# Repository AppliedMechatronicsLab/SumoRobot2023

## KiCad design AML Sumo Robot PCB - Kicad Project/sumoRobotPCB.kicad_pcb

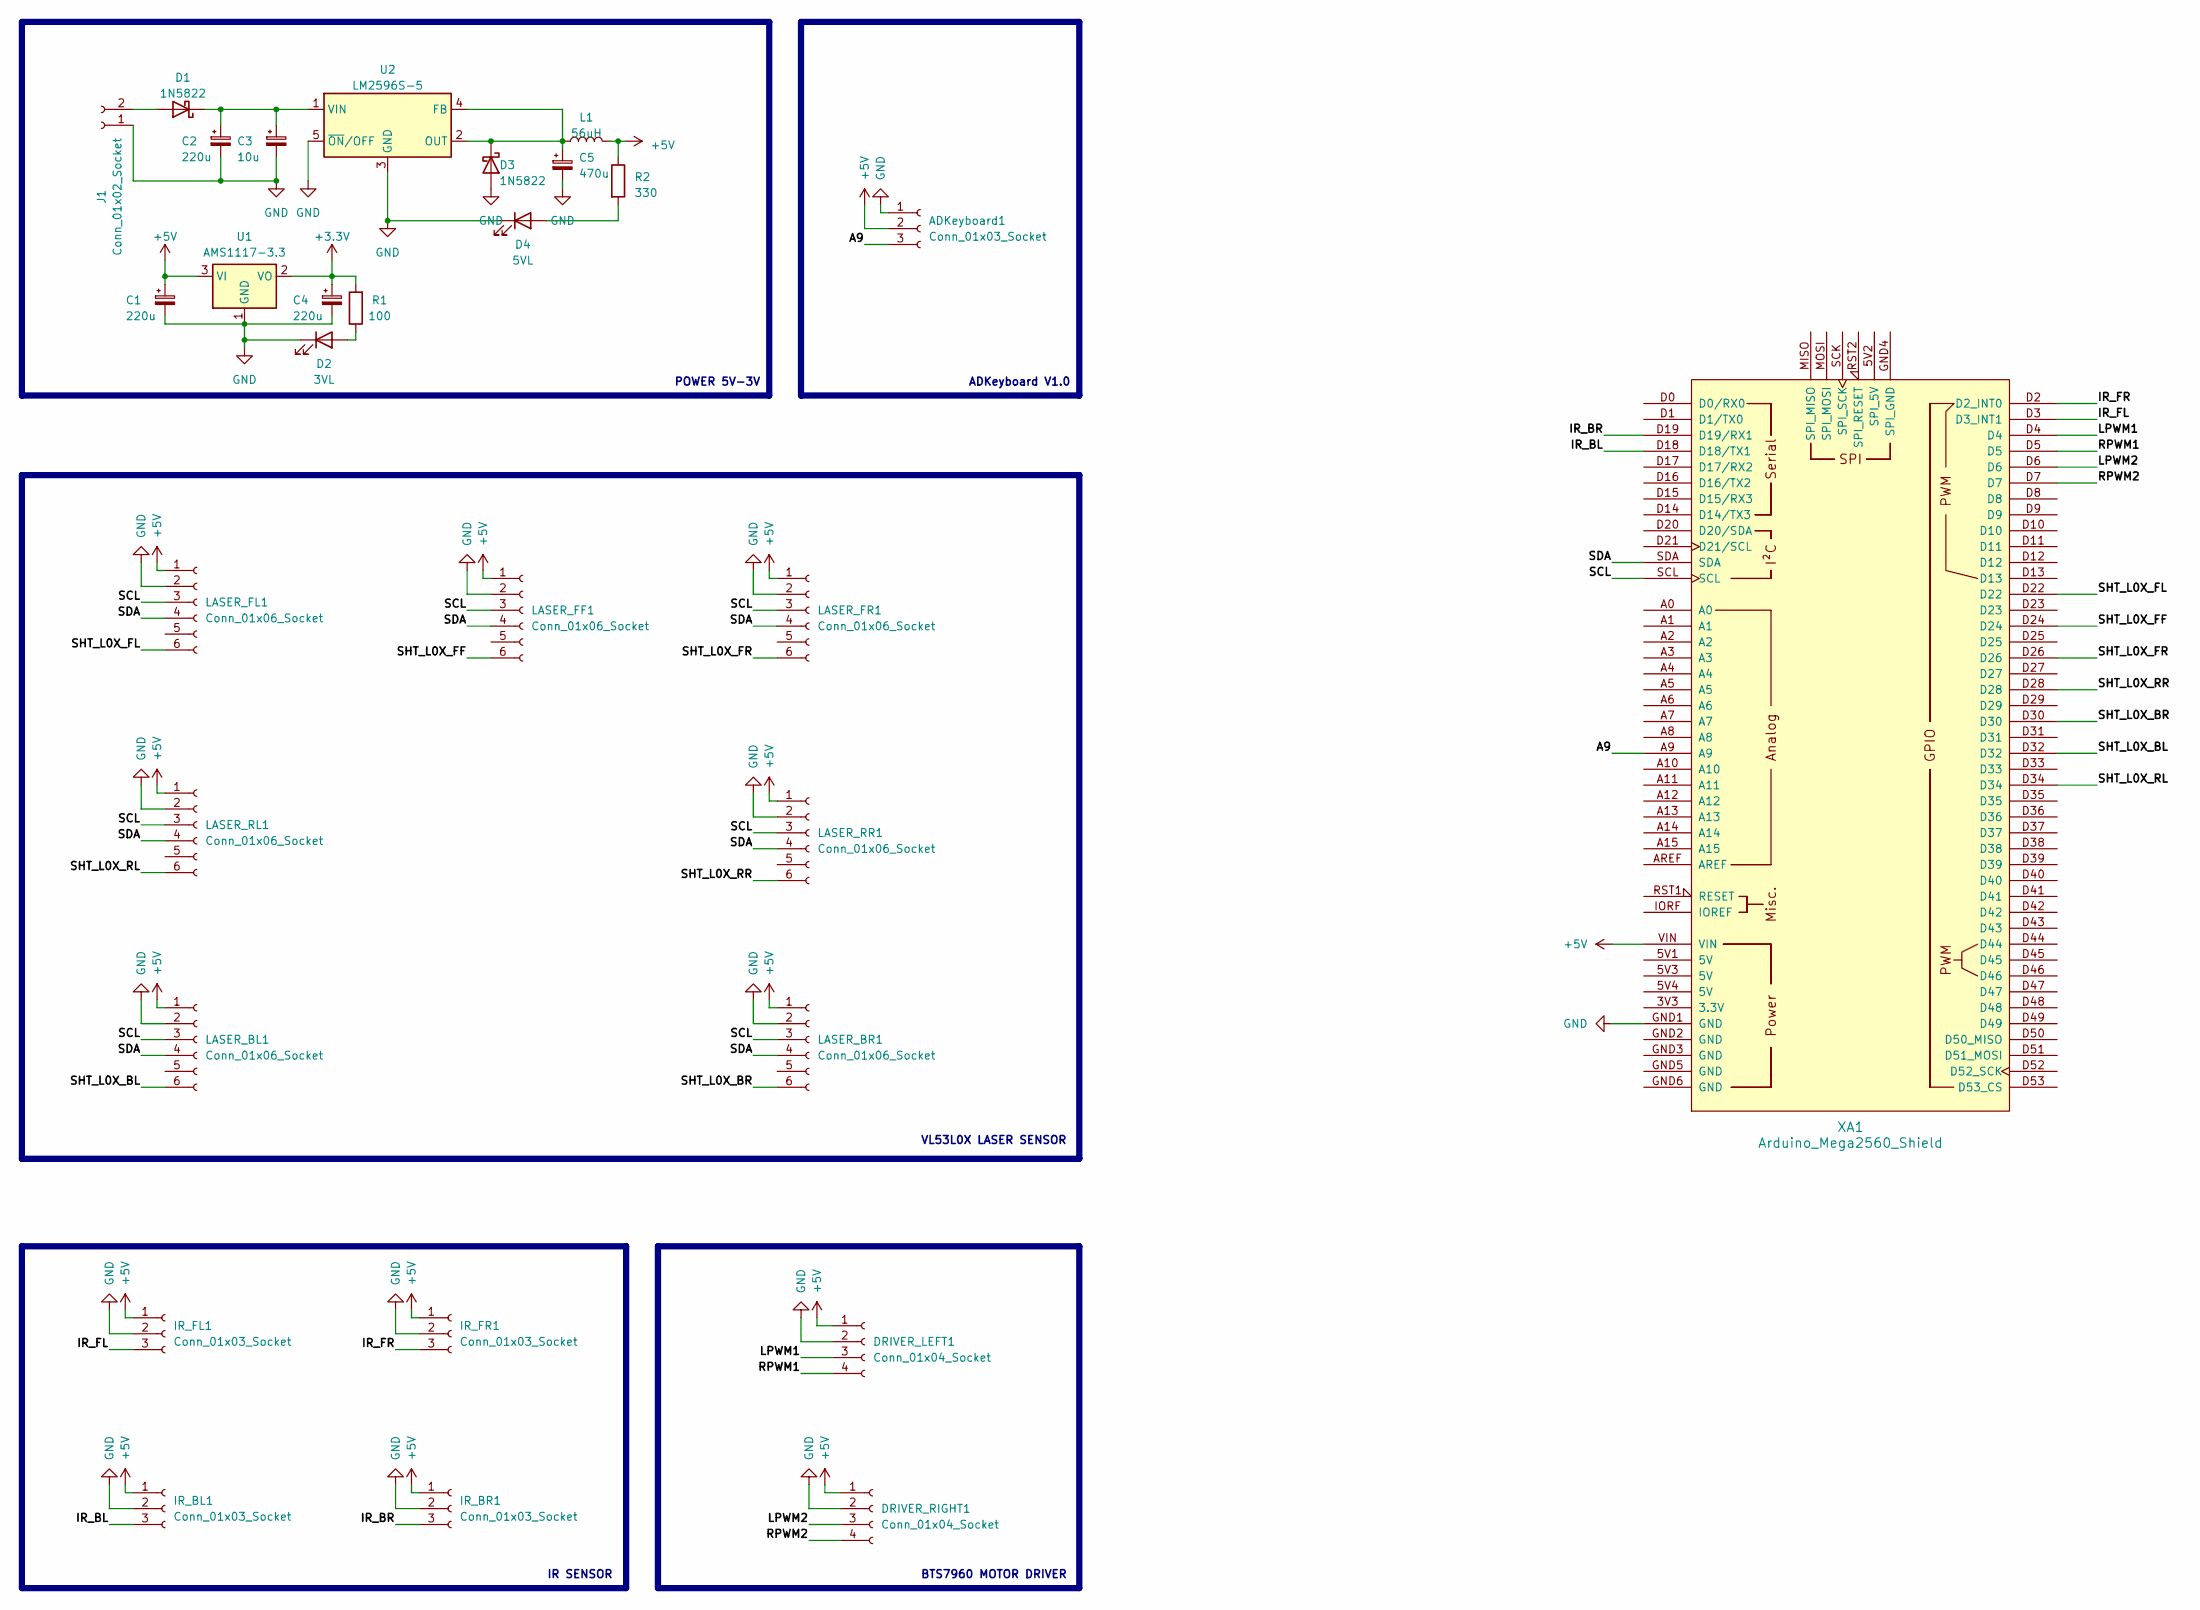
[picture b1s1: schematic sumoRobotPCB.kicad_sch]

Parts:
ADKeyboard1: Conn_01x03_Socket; PinHeader_1x03_P2.54mm_Vertical
C1, C2, C4: 220u; CP_Elec_8x10
C3: 10u; R_0805_2012Metric
C5: 470u; CP_Elec_8x10
D1, D3: 1N5822; D_SMA
D2: 3VL; LED_1206_3216Metric
D4: 5VL; LED_1206_3216Metric
DRIVER_LEFT1: Conn_01x04_Socket; PinHeader_1x04_P2.54mm_Vertical
DRIVER_RIGHT1: Conn_01x04_Socket; PinHeader_1x04_P2.54mm_Vertical
IR_BL1: Conn_01x03_Socket; PinHeader_1x03_P2.54mm_Vertical
IR_BR1: Conn_01x03_Socket; PinHeader_1x03_P2.54mm_Vertical
IR_FL1: Conn_01x03_Socket; PinHeader_1x03_P2.54mm_Vertical
IR_FR1: Conn_01x03_Socket; PinHeader_1x03_P2.54mm_Vertical
J1: Conn_01x02_Socket; JST_VH_B2P-VH_1x02_P3.96mm_Vertical
L1: 56uH
LASER_BL1: Conn_01x06_Socket; PinHeader_1x06_P2.54mm_Vertical
LASER_BR1: Conn_01x06_Socket; PinHeader_1x06_P2.54mm_Vertical
LASER_FF1: Conn_01x06_Socket; PinHeader_1x06_P2.54mm_Vertical
LASER_FL1: Conn_01x06_Socket; PinHeader_1x06_P2.54mm_Vertical
LASER_FR1: Conn_01x06_Socket; PinHeader_1x06_P2.54mm_Vertical
LASER_RL1: Conn_01x06_Socket; PinHeader_1x06_P2.54mm_Vertical
LASER_RR1: Conn_01x06_Socket; PinHeader_1x06_P2.54mm_Vertical
R1: 100; R_0805_2012Metric
R2: 330; R_0805_2012Metric
U1: AMS1117-3.3; SOT-223-3_TabPin2
U2: LM2596S-5; TO-263-5_TabPin3
XA1: Arduino_Mega2560_Shield

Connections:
+3.3V: C4.1, R1.2, U1.2 (VO)
+5V: ADKeyboard1.2, C1.1, DRIVER_LEFT1.1, DRIVER_RIGHT1.1, IR_BL1.1, IR_BR1.1, IR_FL1.1, IR_FR1.1, L1.2, LASER_BL1.1, LASER_BR1.1, LASER_FF1.1, LASER_FL1.1, LASER_FR1.1, LASER_RL1.1, LASER_RR1.1, R2.1, U1.3 (VI), XA1.VIN
/A9: ADKeyboard1.3, XA1.A9
/IR_BL: IR_BL1.3, XA1.D18 (D18/TX1)
/IR_BR: IR_BR1.3, XA1.D19 (D19/RX1)
/IR_FL: IR_FL1.3, XA1.D3 (D3_INT1)
/IR_FR: IR_FR1.3, XA1.D2 (D2_INT0)
/LPWM1: DRIVER_LEFT1.3, XA1.D4
/LPWM2: DRIVER_RIGHT1.3, XA1.D6
/RPWM1: DRIVER_LEFT1.4, XA1.D5
/RPWM2: DRIVER_RIGHT1.4, XA1.D7
/SCL: LASER_BL1.3, LASER_BR1.3, LASER_FF1.3, LASER_FL1.3, LASER_FR1.3, LASER_RL1.3, LASER_RR1.3, XA1.SCL
/SDA: LASER_BL1.4, LASER_BR1.4, LASER_FF1.4, LASER_FL1.4, LASER_FR1.4, LASER_RL1.4, LASER_RR1.4, XA1.SDA
/SHT_L0X_BL: LASER_BL1.6, XA1.D32
/SHT_L0X_BR: LASER_BR1.6, XA1.D30
/SHT_L0X_FF: LASER_FF1.6, XA1.D24
/SHT_L0X_FL: LASER_FL1.6, XA1.D22
/SHT_L0X_FR: LASER_FR1.6, XA1.D26
/SHT_L0X_RL: LASER_RL1.6, XA1.D34
/SHT_L0X_RR: LASER_RR1.6, XA1.D28
GND: ADKeyboard1.1, C1.2, C2.2, C3.2, C4.2, C5.2, D2.1 (K), D3.2 (A), D4.1 (K), DRIVER_LEFT1.2, DRIVER_RIGHT1.2, IR_BL1.2, IR_BR1.2, IR_FL1.2, IR_FR1.2, J1.1, LASER_BL1.2, LASER_BR1.2, LASER_FF1.2, LASER_FL1.2, LASER_FR1.2, LASER_RL1.2, LASER_RR1.2, U1.1 (GND), U2.3 (GND), U2.5 (~ON/OFF), XA1.GND1 (GND)
unnamed: D1.2 (A), J1.2
unnamed: C2.1, C3.1, D1.1 (K), U2.1 (VIN)
unnamed: D2.2 (A), R1.1
unnamed: C5.1, D3.1 (K), L1.1, U2.2 (OUT), U2.4 (FB)
unnamed: D4.2 (A), R2.2

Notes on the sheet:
BTS7960 MOTOR DRIVER
ADKeyboard V1.0
VL53L0X LASER SENSOR
IR SENSOR
POWER 5V-3V

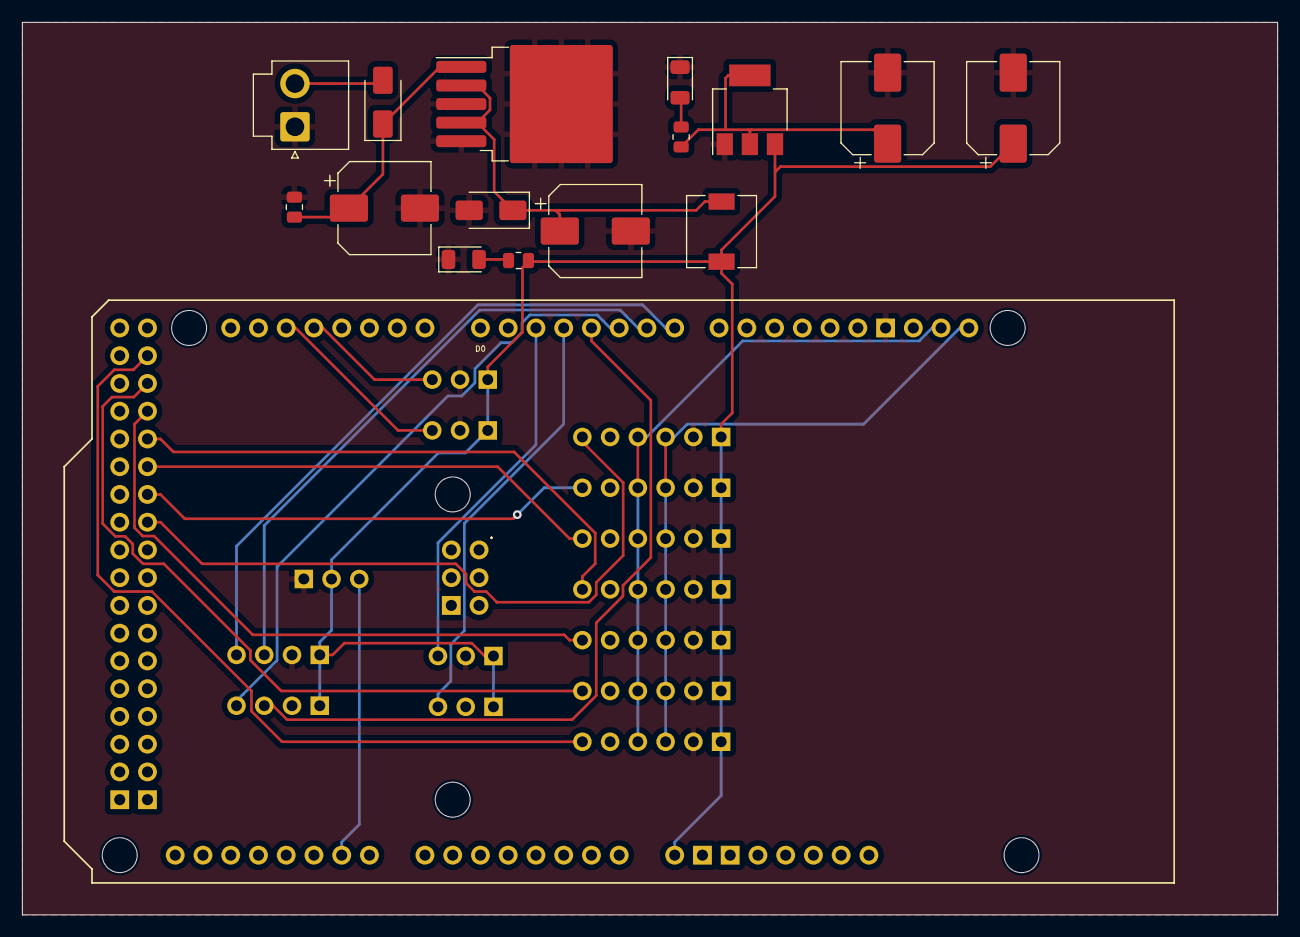
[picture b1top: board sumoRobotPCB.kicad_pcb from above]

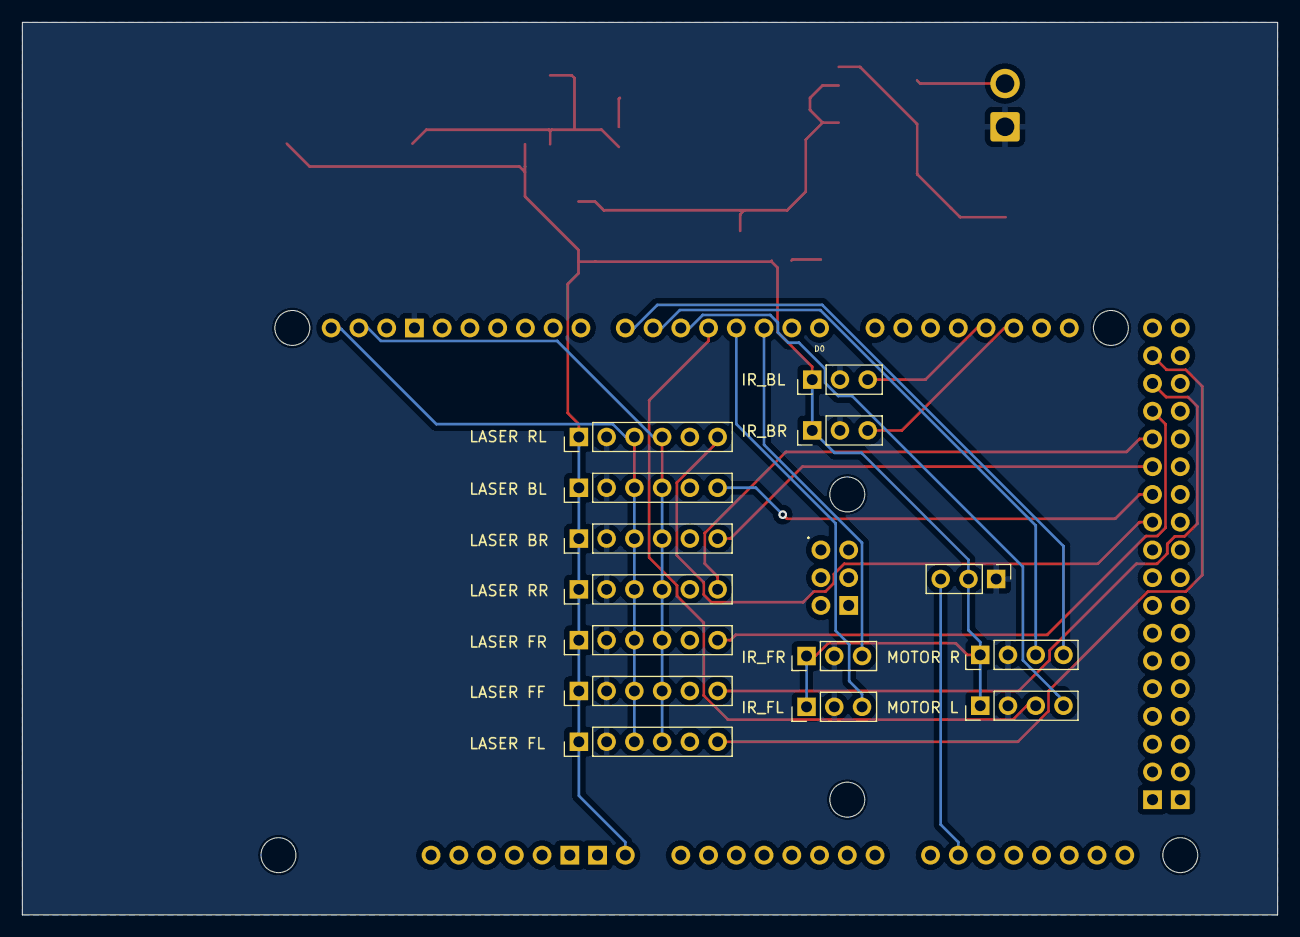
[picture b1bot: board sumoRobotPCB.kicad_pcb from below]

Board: 2 copper layers, 114.9 x 81.7 mm, 30 parts (15 on the bottom side), 26 nets.

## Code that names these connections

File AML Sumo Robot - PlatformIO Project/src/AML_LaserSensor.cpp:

/*
  Library for 7 VL53L0x sensor

  Last updated: 11PM 13/06/2023 UTC+7
  Authors: anmh1205

*/

#include <AML_LaserSensor.h>


// Khởi tạo theo thư viện
VL53L0X FL;
VL53L0X FF;
VL53L0X FR;
VL53L0X RR;
VL53L0X BR;
VL53L0X BL;
VL53L0X RL;


// set the pins to shutdown for all 7 sensors

#define SHT_L0X_FL 22 // XSHUT Pin laser 1
#define SHT_L0X_FF 24 // XSHUT Pin laser 2
#define SHT_L0X_FR 26 // XSHUT Pin laser 3
#define SHT_L0X_RR 28 // XSHUT Pin laser 4
#define SHT_L0X_BR 30 // XSHUT Pin laser 5
#define SHT_L0X_BL 32 // XSHUT Pin laser 6
#define SHT_L0X_RL 34 // XSHUT Pin laser 7


// address we will assign for all 7 sensor
#define L0X_FL_ADDRESS 0x28
#define L0X_FF_ADDRESS 0x30
#define L0X_FR_ADDRESS 0x31
#define L0X_RR_ADDRESS 0x32
#define L0X_BR_ADDRESS 0x33
#define L0X_BL_ADDRESS 0x34
#define L0X_RL_ADDRESS 0x35


// Mảng giá trị cảm biến
int AML_laserSensorValue[8]; 


// bật từng laser lên để cài địa chỉ bằng chân XSHUT
void AML_LaserSensor_setup()
{
  int index = 0;
  pinMode(SHT_L0X_FL, OUTPUT);
  pinMode(SHT_L0X_FF, OUTPUT);
  pinMode(SHT_L0X_FR, OUTPUT);
  pinMode(SHT_L0X_RR, OUTPUT);
  pinMode(SHT_L0X_BR, OUTPUT);
  pinMode(SHT_L0X_BL, OUTPUT);
  pinMode(SHT_L0X_RL, OUTPUT);

  Serial.println(index++);
  // Serial.println("Shutdown pins inited...");

  digitalWrite(SHT_L0X_FL, LOW);
  digitalWrite(SHT_L0X_FF, LOW);
  digitalWrite(SHT_L0X_FR, LOW);
  digitalWrite(SHT_L0X_RR, LOW);
  digitalWrite(SHT_L0X_BR, LOW);
  digitalWrite(SHT_L0X_BL, LOW);
  digitalWrite(SHT_L0X_RL, LOW);

  Serial.println(index++);

  // all unreset
  digitalWrite(SHT_L0X_FL, HIGH);
  digitalWrite(SHT_L0X_FF, HIGH);
  digitalWrite(SHT_L0X_FR, HIGH);
  digitalWrite(SHT_L0X_RR, HIGH);
  digitalWrite(SHT_L0X_BR, HIGH);
  digitalWrite(SHT_L0X_BL, HIGH);
  digitalWrite(SHT_L0X_RL, HIGH);
  delay(10);

  Serial.println(index++);

  // activating L0X_L and reseting L0X_F
  digitalWrite(SHT_L0X_FL, HIGH);
  digitalWrite(SHT_L0X_FF, LOW);
  digitalWrite(SHT_L0X_FR, LOW);
  digitalWrite(SHT_L0X_RR, LOW);
  digitalWrite(SHT_L0X_BR, LOW);
  digitalWrite(SHT_L0X_BL, LOW);
  digitalWrite(SHT_L0X_RL, LOW);

  Serial.println(index++);

  delay(10);
  FL.setAddress(L0X_FL_ADDRESS);

  Serial.println(index++);

  digitalWrite(SHT_L0X_FF, HIGH);
  delay(10);
  FF.setAddress(L0X_FF_ADDRESS);

  Serial.println(index++);

  digitalWrite(SHT_L0X_FR, HIGH);
  delay(10);
  FR.setAddress(L0X_FR_ADDRESS);

  Serial.println(index++);

  digitalWrite(SHT_L0X_RR, HIGH);
  delay(10);
  RR.setAddress(L0X_RR_ADDRESS);

  Serial.println(index++);

  digitalWrite(SHT_L0X_BR, HIGH);
  delay(10);
  BR.setAddress(L0X_BR_ADDRESS);

  Serial.println(index++);

  digitalWrite(SHT_L0X_BL, HIGH);
  delay(10);
  BL.setAddress(L0X_BL_ADDRESS);

  Serial.println(index++);

  digitalWrite(SHT_L0X_RL, HIGH);
  delay(10);
  RL.setAddress(L0X_RL_ADDRESS);

  Serial.println(index++);

  delay(10);

  FL.init();
  FF.init();
  FR.init();
  RR.init();
  BR.init();
  BL.init();
  RL.init();

  Serial.println(index++);

  // Gắn cờ lỗi
  FL.setTimeout(500);
  FF.setTimeout(500);
  FR.setTimeout(500);
  RR.setTimeout(500);
  BR.setTimeout(500);
  BL.setTimeout(500);
  RL.setTimeout(500);

  Serial.println(index++);

  // // reduce timing budget to 20 ms (default is about 33 ms)
  // FL.setMeasurementTimingBudget(20);
  // FF.setMeasurementTimingBudget(20);
  // FR.setMeasurementTimingBudget(20);
  // RR.setMeasurementTimingBudget(20);
  // BR.setMeasurementTimingBudget(20);
  // BL.setMeasurementTimingBudget(20);
  // RL.setMeasurementTimingBudget(20);

  FL.startContinuous(10);
  FF.startContinuous(10);
  FR.startContinuous(10);
  RR.startContinuous(10);
  BR.startContinuous(10);
  BL.startContinuous(10);
  RL.startContinuous(10);

  Serial.println(index++);
}


int AML_LaserSensor_readSingle(int laserNumber)
{
    AML_LaserSensor_readAll(AML_laserSensorValue);
    return AML_laserSensorValue[laserNumber];
}

// Đọc laser (không ghi ra serial)
void AML_LaserSensor_readAll(int *userArrayAddress)
{
  int index = 0;

  // dùng ++index khù khoằm này để copy patse cho nhanh, đỡ phải gõ
  AML_laserSensorValue[++index] = FL.readRangeContinuousMillimeters();
  *(userArrayAddress + index) = FL.readRangeContinuousMillimeters();

  AML_laserSensorValue[++index] = FF.readRangeContinuousMillimeters();
  *(userArrayAddress + index) = FF.readRangeContinuousMillimeters();

  AML_laserSensorValue[++index] = FR.readRangeContinuousMillimeters();
  *(userArrayAddress + index) = FR.readRangeContinuousMillimeters();

  AML_laserSensorValue[++index] = RR.readRangeContinuousMillimeters();
  *(userArrayAddress + index) = RR.readRangeContinuousMillimeters();

  AML_laserSensorValue[++index] = BR.readRangeContinuousMillimeters();
  *(userArrayAddress + index) = BR.readRangeContinuousMillimeters();

  AML_laserSensorValue[++index] = BL.readRangeContinuousMillimeters();
  *(userArrayAddress + index) = BL.readRangeContinuousMillimeters();

  AML_laserSensorValue[++index] = RL.readRangeContinuousMillimeters();
  *(userArrayAddress + index) = RL.readRangeContinuousMillimeters();
}


// Hàm này giống hệt readLaserSensor(), khác mỗi cái có ghi ra serial để xem giá trị
void AML_LaserSensor_readAllTest(int *userArrayAddress)
{
  int index = 0;

  AML_laserSensorValue[++index] = FL.readRangeContinuousMillimeters();
  *(userArrayAddress + index) = FL.readRangeContinuousMillimeters();
  Serial.print(AML_laserSensorValue[index]);

  Serial.print("   ");

  AML_laserSensorValue[++index] = FF.readRangeContinuousMillimeters();
  *(userArrayAddress + index) = FF.readRangeContinuousMillimeters();
  Serial.print(AML_laserSensorValue[index]);

  Serial.print("   ");

  AML_laserSensorValue[++index] = FR.readRangeContinuousMillimeters();
  *(userArrayAddress + index) = FR.readRangeContinuousMillimeters();
  Serial.print(AML_laserSensorValue[index]);

  Serial.print("   ");

  AML_laserSensorValue[++index] = RR.readRangeContinuousMillimeters();
  *(userArrayAddress + index) = RR.readRangeContinuousMillimeters();
  Serial.print(AML_laserSensorValue[index]);

  Serial.print("   ");

  AML_laserSensorValue[++index] = BR.readRangeContinuousMillimeters();
  *(userArrayAddress + index) = BR.readRangeContinuousMillimeters();
  Serial.print(AML_laserSensorValue[index]);

  Serial.print("   ");

  AML_laserSensorValue[++index] = BL.readRangeContinuousMillimeters();
  *(userArrayAddress + index) = BL.readRangeContinuousMillimeters();
  Serial.print(AML_laserSensorValue[index]);

  Serial.print("   ");

  AML_laserSensorValue[++index] = RL.readRangeContinuousMillimeters();
  *(userArrayAddress + index) = RL.readRangeContinuousMillimeters();
  Serial.print(AML_laserSensorValue[index]);

  Serial.println("   ");
}

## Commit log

2023-08-21 project init
2023-08-21 add PCB and Document file
2023-08-25 add 3D file
